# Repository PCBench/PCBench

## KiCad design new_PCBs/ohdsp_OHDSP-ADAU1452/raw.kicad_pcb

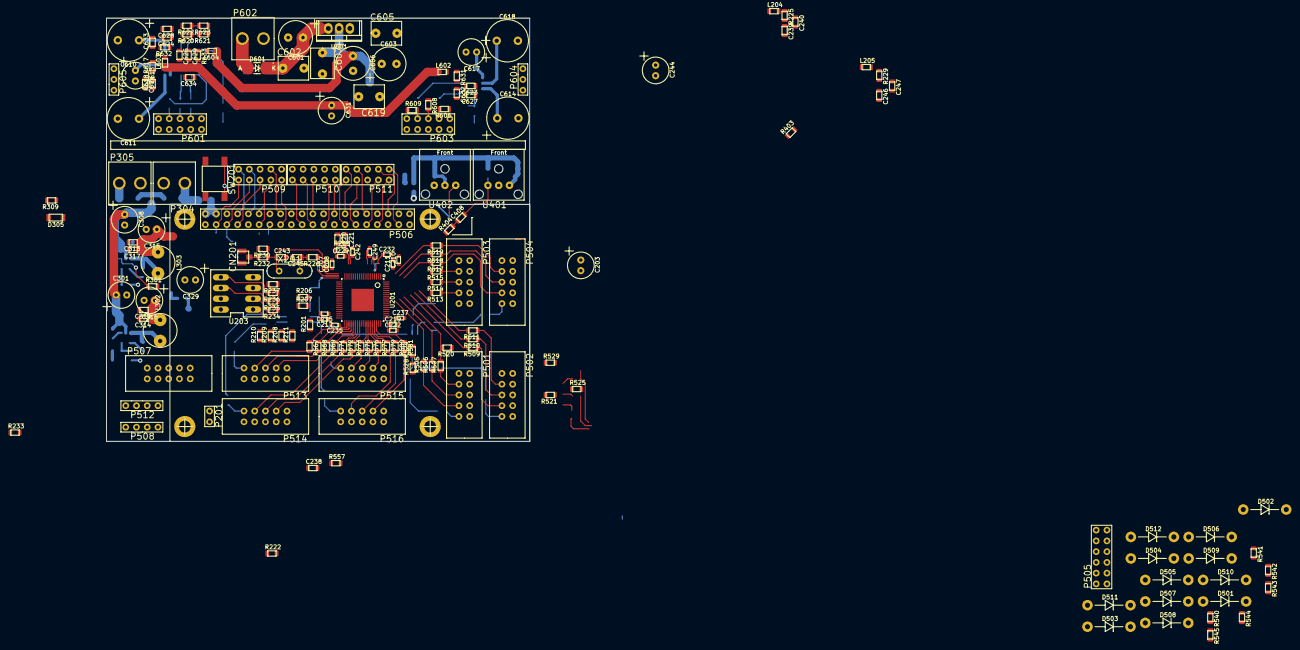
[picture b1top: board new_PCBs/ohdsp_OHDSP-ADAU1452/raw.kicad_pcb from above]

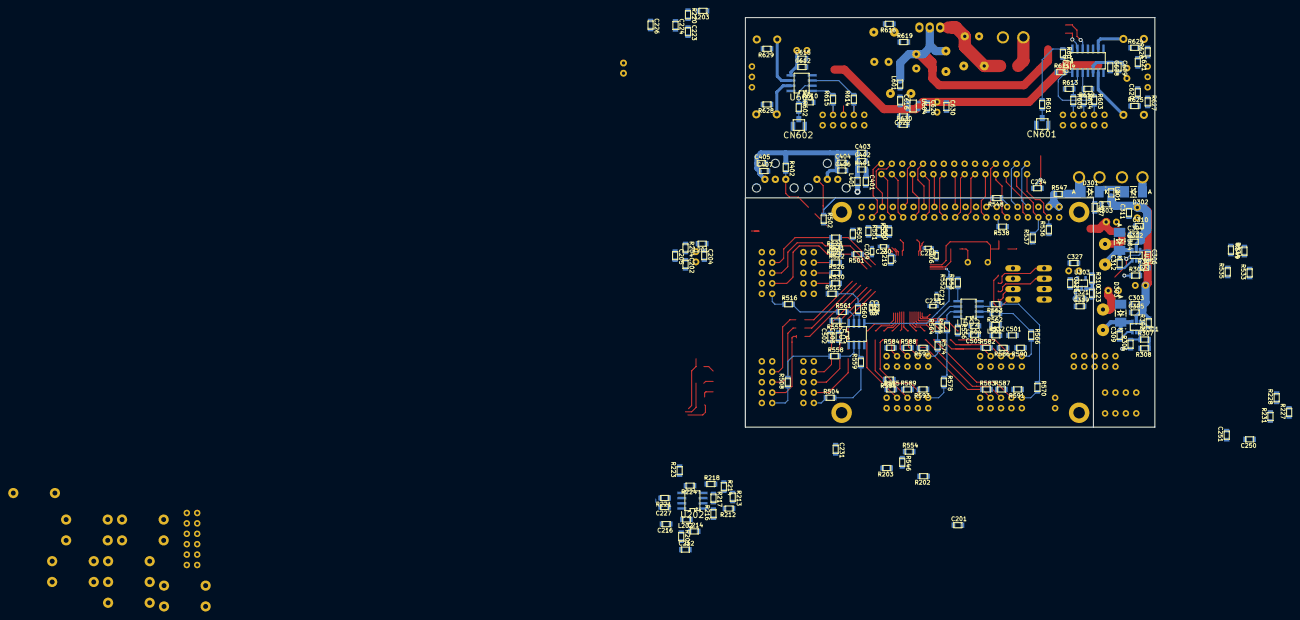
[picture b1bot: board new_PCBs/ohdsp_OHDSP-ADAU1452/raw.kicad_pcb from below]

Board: 4 copper layers, 100.0 x 100.0 mm, 376 parts (188 on the bottom side), 240 nets.

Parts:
C201, C205, C216, C226, C227, C231, C234, C238, C250, C304, C305, C311, C317, C318, C321, C325, C403, C406, C407, C503, C505, C604, C608, C612, C623, C624, C625, C626: 100n; SMD-0805
C202, C212, C223, C239, C246, C307, C401, C501, C632, C633, C634: 100p; SMD-0805
C203, C244, C301, C308, C315, C316, C329: 220u; CAP-TH-D6.3mmP2.5mm
C204, C224, C240, C247, C302, C303, C310, C313, C314, C319, C327, C402, C404, C405, C502, C504, C609, C615, C616, C627, C628, C629, C630: 22u; SMD-0805
C206, C209, C213, C218, C228, C230, C233, C236: 1u; SMD-0603
C207, C210, C215, C219, C229, C232, C235, C237, C242, C249: 100n; SMD-0603
C208, C211, C217, C222: 10n; SMD-0603
C214, C251, C306, C323: 1u; SMD-0805
C220: 5n6; SMD-0805
C221: 150p; SMD-0805
C243, C245: 33p; SMD-0805
C309, C312, C408, C622: 10n; SMD-0805
C601, C603, C606: 220u; CAP-TH-D8mmP3.5mm
C602, C605, C607, C619: 10n; CAP_TH_5mm
C610, C611, C614, C618: 100u; CAP-TH-D10mmP5mm
C613, C617, C631: 100u; CAP-TH-D6.3mmP2.5mm
C620, C621: 1n; SMD-0805
CN201, CN601, CN602: COAX; CONN-RF-UFL
D301, D302, D303, D304, D601: SS24T3G; DIODE-SMB
D305: LED; SMD-1206
D501, D502, D503, D504, D505, D506, D507, D508, D509, D510, D511, D512: 1N5818; DIODE-DO-41
L201, L202, L203, L204, L205, L301, L401, L501, L601, L602, L603, L604: 600R@100MHz; SMD-0805
L302: 744772220; PASSIVE-TH-IND-WURTH-5mm
L303: 744772047; PASSIVE-TH-IND-WURTH-5mm
P201: CONN_2x1; CONN_SIL_2
P301, P302, P303, P306: PIN; MNT_HOLE_2.5mm
P304, P305, P602: CONN_2x1; CONN-SCREW-2WAY-5mm-5.08mm
P501, P502, P503, P504, P507, P513, P514, P515, P516: CONN_02X05; CONN_DIL_2X5_BOX
P505: CONN_6X2; CONN_DIL_2X6
P506: CONN_02X20; CONN_DIL_2X20
P508, P512: CONN_4x1; CONN_SIL_4
P509, P510, P511, P601, P603: CONN_02X05; CONN_DIL_2X5
P604, P605: CONN_3x1; CONN_SIL_3
R201, R221, R538, R555, R556: 1k; SMD-0805
R202, R203, R626, R627: 2k2; SMD-0805
R204, R205, R220, R225, R229, R303, R401, R532, R631, R632, R633: 47R; SMD-0805
R206, R207, R212, R219, R234, R235, R236, R237, R308, R403, R504, R505, R506, R507, R508, R509, R510, R511, R512, R513, R514, R515, R516, R517, R518, R519, R533, R534, R535, R536, R537, R539, R546, R547, R548, R549, R550, R551, R554, R557, R601, R602, R614, R615: 0R; SMD-0805
R208, R209, R216, R230, R232, R233, R501, R502, R503, R520, R521, R522, R523, R524, R525, R526, R527, R528, R529, R530, R531, R582, R583, R584, R585, R586, R587, R588, R589, R590, R591, R592, R593, R594, R606, R607, R609, R610, R611, R612, R613, R618, R621, R623: N/F; SMD-0805
R210, R211, R227, R228, R231, R307, R402, R608, R617, R620, R622, R624, R625, R628, R629, R630: 10k; SMD-0805
R213: 12k; SMD-0805
R214: 3k3; SMD-0805
R215: 4k3; SMD-0805
R217: 3k; SMD-0805
R218: 3k6; SMD-0805
R222, R223, R226: 100R; SMD-0805
R224, R301, R302, R310: 100k; SMD-0805
R304: 47k; SMD-0805
R305: 97k6; SMD-0805
R306: 39k; SMD-0805
R309: 470R; SMD-0805
R404: 22R; SMD-0805
R540, R541, R542, R543, R544, R545: 4k7; SMD-0805
R552, R553: 75R; SMD-0805
R558, R559, R560, R561, R562, R563, R564, R565, R566, R567, R568, R569, R570, R571, R572, R573, R574, R575, R576, R577, R578, R579, R580, R581, R603, R604, R605: 27R; SMD-0805
R616: 360R; SMD-0805
R619: 120R; SMD-0805
SW201: SWITCH; SW_TACT_SMD
U201: ADAU1452WBCPZ; IC-LFCSP72-HANDFIT
U202: ADM13307-5ARZ; IC_SOIC_8
U203: 25AA1024; IC_DIP_8
U301, U302: IC-REG-XRP7659ISTR-F; IC-SOT23-6
U303, U604: IC-REG-XC6210B332MR; IC-SOT25
U401: IC-SPDIF-RX-OPTO; IC_SPDIF_OPTO
U402: IC-SPDIF-TX-OPTO; IC_SPDIF_OPTO
U501, U502: NB3L553; IC_SOIC_8
U601: IC-REG-LM317-TO220; TO-220
U602: IC-DAC-WM8501; IC_SOIC_14
U603: IC-ADC-WM8783; IC_SOIC_8
X201: 24M576; XTAL_HC49_TH

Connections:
+5V: D301.1, P304.1, R547.2
/ADAU1452/ADAU_SPDIF_RX: R404.1, U201.4
/ADAU1452/ADAU_SPDIF_TX: R403.1, U201.5
/ADAU1452/ADCIN_BCLK0: R506.2, R524.2, U201.58
/ADAU1452/ADCIN_BCLK1: R510.2, R525.2, U201.61
/ADAU1452/ADCIN_BCLK2: R514.2, R526.2, U201.66
/ADAU1452/ADCIN_BCLK3: R502.2, R518.2, R527.2, U201.69
/ADAU1452/ADCIN_LRCLK0: R505.2, R528.2, U201.57
/ADAU1452/ADCIN_LRCLK1: R509.2, R529.2, U201.60
/ADAU1452/ADCIN_LRCLK2: R513.2, R530.2, U201.65
/ADAU1452/ADCIN_LRCLK3: R501.2, R517.2, R531.2, U201.68
/ADAU1452/ADCIN_SDATA0: R507.2, R520.2, U201.59
/ADAU1452/ADCIN_SDATA1: R511.2, R521.2, U201.62
/ADAU1452/ADCIN_SDATA2: R515.2, R522.2, U201.67
/ADAU1452/ADCIN_SDATA3: R503.2, R519.2, R523.2, U201.70
/ADAU1452/AVDD: C247.1, C249.1, L205.2, R229.1, U201.7
/ADAU1452/DACOUT_BCLK0: R568.1, U201.40
/ADAU1452/DACOUT_BCLK1: R572.1, U201.43
/ADAU1452/DACOUT_BCLK2: R576.1, U201.48
/ADAU1452/DACOUT_BCLK3: R580.1, U201.51
/ADAU1452/DACOUT_LRCLK0: R567.1, U201.39
/ADAU1452/DACOUT_LRCLK1: R571.1, U201.42
/ADAU1452/DACOUT_LRCLK2: R575.1, U201.47
/ADAU1452/DACOUT_LRCLK3: R579.1, U201.50
/ADAU1452/DACOUT_SDATA0: R569.1, U201.41
/ADAU1452/DACOUT_SDATA1: R573.1, U201.44
/ADAU1452/DACOUT_SDATA2: R577.1, U201.49
/ADAU1452/DACOUT_SDATA3: R581.1, U201.52
/ADAU1452/DSP_RESET: C238.1, R222.1, U201.24
/ADAU1452/DVDD: C203.1, C204.1, C205.1, C206.1, C207.1, C208.1, C209.1, C210.1, C211.1, C213.1, C215.1, C217.1, C218.1, C219.1, C222.1, L201.2, R204.1, U201.20, U201.35, U201.53, U201.71
/ADAU1452/GLB_RESET: R223.1, R546.1, R557.1
/ADAU1452/I2C_SCL: P507.1, P508.1, P512.1, R202.2, R207.1, R537.1
/ADAU1452/I2C_SDA: P507.3, P508.2, P512.2, R203.2, R206.1, R536.1
/ADAU1452/IOVDD: C224.1, C226.1, C228.1, C229.1, C230.1, C232.1, C233.1, C235.1, C236.1, C237.1, L203.2, R208.1, R209.1, R220.1, U201.2, U201.18, U201.38, U201.56
/ADAU1452/MAN_RST_IN: C234.1, R221.2, R538.1, R554.2, SW201.1
/ADAU1452/MCLK: R552.2, R553.2, U201.23
/ADAU1452/M_MISO: R233.2, R234.2, U203.2
/ADAU1452/M_MOSI: R236.2, U203.5
/ADAU1452/M_SCLK: R235.2, U203.6
/ADAU1452/M_SS: R227.2, R237.2, U203.1
/ADAU1452/PVDD: C220.1, C221.1, C240.1, C242.1, L204.2, R225.1, U201.15
/ADAU1452/SELFBOOT: P201.1, R201.2, U201.34
/ADAU1452/XTALIN: C243.1, R230.1, R232.1, U201.21, X201.1
/ADAU1452/XTALOUT: R226.1, U201.22
/Connectors/AUXADCIN_1: D501.1, D502.2, R540.2, U201.8
/Connectors/AUXADCIN_2: D503.1, D504.2, R541.2, U201.9
/Connectors/AUXADCIN_3: D505.1, D506.2, R542.2, U201.10
/Connectors/AUXADCIN_4: D507.1, D508.2, R543.2, U201.11
/Connectors/AUXADCIN_5: D509.1, D510.2, R544.2, U201.12
/Connectors/AUXADCIN_6: D511.1, D512.2, R545.2, U201.13
/Connectors/MCLKA1: R508.2, R558.1
/Connectors/MCLKA2: R504.2, R559.1
/Connectors/MCLKA3: R512.2, R560.1
/Connectors/MCLKA4: R516.2, R561.1
/Connectors/MCLKB1: R562.1, R566.1
/Connectors/MCLKB2: R563.1, R570.1
/Connectors/MCLKB3: R564.1, R574.1
/Connectors/MCLKB4: R565.1, R578.1
/Connectors/PI_GP4: P506.7, P509.5
/Connectors/PI_GP5: P506.29, P511.3
/Connectors/PI_GP6: P506.31, P511.7
/Connectors/PI_GP12: P506.32, P511.4
/Connectors/PI_GP13: P506.33, P511.9
/Connectors/PI_GP14: P506.8, P509.2
/Connectors/PI_GP15: P506.10, P509.4
/Connectors/PI_GP16: P506.36, P511.8
/Connectors/PI_GP17: P506.11, P509.7
/Connectors/PI_GP22: P506.15, P509.9
/Connectors/PI_GP23: P506.16, P509.8
/Connectors/PI_GP24: P506.18, P509.10
/Connectors/PI_GP25: P506.22, P510.5
/Connectors/PI_GP26: P506.37, P511.10
/Connectors/PI_IDSC: P506.28, P511.2
/Connectors/PI_IDSD: P506.27, P511.1
/Connectors/PI_MISO: P506.21, P510.3, R534.2
/Connectors/PI_MOSI: P506.19, P510.1, R533.2
/Connectors/PI_SCL: P506.5, P509.3, R537.2
/Connectors/PI_SCLK: P506.23, P510.7, R535.2
/Connectors/PI_SDA: P506.3, P509.1, R536.2
/Connectors/RPI_BCLK: R502.1, R548.2
/Connectors/RPI_CS2: P506.26, P510.9
/Connectors/RPI_LRCLK: R501.1, R539.1
/Connectors/RPI_SDATA_IN: R550.2, R594.2
/Connectors/RPI_SDATA_OUT: R503.1, R551.2
/SimpleADCDAC/ADC_AVDD: C623.1, C627.1, L602.2, R631.1, U603.8
/SimpleADCDAC/DAC5v: C606.1, C607.1, L601.2, L604.1, R619.2, U601.2
/SimpleADCDAC/DAC_AVDD: C625.1, C629.1, L604.2, R633.1, U602.8
/SimpleADCDAC/DAC_DVDD: C624.1, C628.1, L603.2, R617.2, R620.2, R622.2, R632.1, U602.11
/SimpleADCDAC/DEMP: R622.1, R623.2, U602.12
/SimpleADCDAC/EN: C604.1, R617.1, R618.2, U602.4
/SimpleADCDAC/FMT: R620.1, R621.2, U602.13
GNDA: C601.2, C602.2, C603.2, C604.2, C605.2, C606.2, C607.2, C608.2, C609.2, C612.2, C613.2, C615.2, C616.2, C617.2, C619.2, C620.2, C621.2, C622.2, C623.2, C624.2, C625.2, C626.2, C627.2, C628.2, C629.2, C630.2, C631.2, C632.2, C633.2, C634.2, CN601.2, CN602.2, P601.1, P601.2, P601.3, P601.5, P601.7, P601.9, P601.10, P602.2, P603.1, P603.2, P603.3, P603.5, P603.7, P603.9, P603.10, P604.2, P605.2, R606.1, R607.2, R608.1, R609.1, R610.2, R611.1, R612.1, R613.1, R616.2, R618.1, R621.1, R623.1, R624.1, R625.1, R628.1, R629.1, U602.7, U602.10, U603.4, U604.2
GNDD: C201.2, C202.2, C203.2, C204.2, C205.2, C206.2, C207.2, C208.2, C209.2, C210.2, C211.2, C212.2, C213.2, C214.2, C215.2, C216.2, C217.2, C218.2, C219.2, C222.2, C223.2, C224.2, C226.2, C227.2, C228.2, C229.2, C230.2, C231.2, C232.2, C233.2, C234.2, C235.2, C236.2, C237.2, C238.2, C239.2, C240.2, C242.2, C243.2, C244.2, C245.2, C246.2, C247.2, C249.2, C250.2, C251.2, C301.2, C302.1, C303.1, C304.1, C305.1, C306.2, C307.2, C308.2, C310.1, C311.1, C313.2, C314.2, C315.2, C316.2, C317.2, C318.2, C319.2, C321.2, C323.2, C325.2, C327.2, C329.2, C401.2, C402.2, C403.2, C404.2, C405.2, C406.2, C407.2, C501.2, C502.2, C503.2, C504.2, C505.2, CN201.2, D303.1, D304.1, D305.2, D502.1, D504.1, D506.1, D508.1, D510.1, D512.1, P201.2, P301.1, P302.1, P303.1, P304.2, P305.2, P306.1, P501.1, P501.3, P501.5, P501.7, P501.9, P501.10, P502.1, P502.3, P502.5, P502.7, P502.9, P502.10, P503.1, P503.3, P503.5, P503.7, P503.9, P503.10, P504.1, P504.3, P504.5, P504.7, P504.9, P504.10, P505.1, P505.3, P505.5, P505.7, P505.9, P505.11, P506.6, P506.9, P506.14, P506.20, P506.25, P506.30, P506.34, P506.39, P508.3, P509.6, P510.2, P510.4, P510.6, P510.8, P510.10, P511.5, P511.6, P512.3, P513.1, P513.3, P513.5, P513.7, P513.9, P513.10, P514.1, P514.3, P514.5, P514.7, P514.9, P514.10, P515.1, P515.3, P515.5, P515.7, P515.9, P515.10, P516.1, P516.3, P516.5, P516.7, P516.9, P516.10, R210.1, R211.1, R216.1, R217.1, R218.1, R219.1, R224.1, R230.2, R305.2, R308.2, R520.1, R521.1, R522.1, R523.1, R524.1, R525.1, R526.1, R527.1, R528.1, R529.1, R530.1, R531.1, R582.1, R583.1, R584.1, R585.1, R586.1, R587.1, R588.1, R589.1, R590.1, R591.1, R592.1, R593.1, SW201.2, U201.1, U201.6, U201.14, U201.17, U201.19, U201.25, U201.36, U201.37, U201.54, U201.55, U201.72, U201.EP1, U202.4, U203.4, U301.2, U302.2, U303.2, U401.2, U402.3, U501.4, U502.4
unnamed: C202.1, R204.2
unnamed: C212.1, R205.2
unnamed: C214.1, C216.1, L202.2, R205.1, U202.8
unnamed: C220.2, R215.1
unnamed: C221.2, R215.2, U201.16
unnamed: C223.1, R220.2
unnamed: C227.1, R221.1, U202.7
unnamed: C231.1, R222.2, R223.2, R224.2, U202.6
unnamed: C239.1, R225.2
unnamed: C245.1, R226.2, X201.2
unnamed: C246.1, R229.2
unnamed: C306.1, R301.1, U302.4
unnamed: C307.1, R303.2
unnamed: C309.1, U301.1
unnamed: C309.2, D303.2, L302.1, U301.6
unnamed: C312.1, U302.1
unnamed: C312.2, D304.2, L303.1, U302.6
unnamed: C323.1, R310.2, U303.3
unnamed: C401.1, R401.2
unnamed: C402.1, C403.1, C404.1, C405.1, C406.1, C407.1, L401.2, R401.1, R402.1, U401.1, U402.2
unnamed: C408.1, R404.2
unnamed: C408.2, R402.2, U401.3
unnamed: C501.1, R532.2
unnamed: C502.1, C503.1, C504.1, C505.1, L501.2, R532.1, R555.2, R556.2, U501.1, U502.1
unnamed: C601.1, C602.1, D601.2, U601.3
unnamed: C603.1, C605.1, R616.1, R619.1, U601.1
unnamed: C608.1, C609.1, C613.1, U602.5
unnamed: C610.1, U602.9
unnamed: C610.2, R624.2, R626.2
unnamed: C611.1, U602.6
unnamed: C611.2, R625.2, R627.2
unnamed: C612.1, C615.1, C617.1, U603.5
unnamed: C614.1, U603.7
unnamed: C614.2, P604.1, R628.2
unnamed: C616.1, C619.1, L601.1, R630.1, U604.1
unnamed: C618.1, U603.6
unnamed: C618.2, P604.3, R629.2
unnamed: C620.1, P605.3, R627.1
unnamed: C621.1, P605.1, R626.1
unnamed: C622.1, R630.2, U604.3
unnamed: C626.1, C630.1, C631.1, L602.1, L603.1, U604.5
unnamed: C632.1, R631.2
unnamed: C633.1, R632.2
unnamed: C634.1, R633.2
unnamed: CN201.1, R232.2
unnamed: CN601.1, R601.2
unnamed: CN602.1, R602.2
unnamed: D301.2, D302.2, L301.1
unnamed: D302.1, P305.1
unnamed: D305.1, R309.2
unnamed: D601.1, P602.1
unnamed: P501.2, R504.1
unnamed: P501.4, R505.1
unnamed: P501.6, R506.1
unnamed: P501.8, R507.1
unnamed: P502.2, R508.1
unnamed: P502.4, R509.1
unnamed: P502.6, R510.1
unnamed: P502.8, R511.1
unnamed: P503.2, R512.1
unnamed: P503.4, R513.1
unnamed: P503.6, R514.1
unnamed: P503.8, R515.1
unnamed: P504.2, R516.1
unnamed: P504.4, R517.1
unnamed: P504.6, R518.1
unnamed: P504.8, R519.1
unnamed: P505.2, R540.1
unnamed: P505.4, R541.1
unnamed: P505.6, R542.1
unnamed: P505.8, R543.1
unnamed: P505.10, R544.1
unnamed: P505.12, R545.1
unnamed: P506.2, P506.4, R547.1
unnamed: P506.12, R548.1
unnamed: P506.13, R538.2
unnamed: P506.24, R549.1
unnamed: P506.35, R539.2
unnamed: P506.38, R550.1
unnamed: P506.40, R551.1
unnamed: P507.6, R554.1
unnamed: P508.4, R546.2
unnamed: P512.4, R557.2
unnamed: P513.2, R566.2
unnamed: P513.4, R567.2, R590.2
unnamed: P513.6, R568.2, R586.2
unnamed: P513.8, R569.2, R582.2
unnamed: P514.2, R570.2
unnamed: P514.4, R571.2, R591.2
unnamed: P514.6, R572.2, R587.2
unnamed: P514.8, R573.2, R583.2
unnamed: P515.2, R574.2
unnamed: P515.4, R575.2, R592.2
unnamed: P515.6, R576.2, R588.2
unnamed: P515.8, R577.2, R584.2
unnamed: P516.2, R578.2
unnamed: P516.4, R579.2, R593.2
unnamed: P516.6, R580.2, R589.2
unnamed: P516.8, R581.2, R585.2, R594.1
unnamed: P601.4, R603.2
unnamed: P601.6, R604.2
unnamed: P601.8, R605.2
unnamed: P603.4, R609.2, R614.1
unnamed: P603.6, R608.2
unnamed: P603.8, R606.2, R615.1
unnamed: R206.2, U201.30
unnamed: R207.2, U201.31
unnamed: R208.2, R211.2, U201.33
unnamed: R209.2, R210.2, U201.32
unnamed: R212.2, R216.2, U202.1
unnamed: R213.2, R217.2, U202.2
unnamed: R214.2, R218.2, U202.3
unnamed: R219.2, U201.3
unnamed: R228.2, U203.3
unnamed: R231.2, U203.7
unnamed: R234.1, U201.29
unnamed: R235.1, U201.28
unnamed: R236.1, U201.27
unnamed: R237.1, U201.26
unnamed: R302.1, U301.4
unnamed: R304.2, R305.1, U302.3
unnamed: R306.2, R307.1, U301.3
unnamed: R307.2, R308.1
unnamed: R403.2, U402.1
unnamed: R552.1, U501.5
unnamed: R553.1, U502.5
unnamed: R555.1, U501.8
unnamed: R556.1, U502.8
unnamed: R558.2, U501.2
unnamed: R559.2, U501.3
unnamed: R560.2, U501.6
unnamed: R561.2, U501.7
unnamed: R562.2, U502.2
unnamed: R563.2, U502.3
unnamed: R564.2, U502.6
unnamed: R565.2, U502.7
unnamed: R601.1, R607.1, U602.14
unnamed: R602.1, R610.1, U603.2
unnamed: R603.1, R611.2, U602.1
unnamed: R604.1, R612.2, U602.3
unnamed: R605.1, R613.2, U602.2
unnamed: R614.2, U603.3
unnamed: R615.2, U603.1
VAA: C201.1, C244.1, C250.1, C251.1, C325.1, C327.1, C329.1, D501.2, D503.2, D505.2, D507.2, D509.2, D511.2, L202.1, L203.1, L204.1, L205.1, L401.1, L501.1, R201.1, R202.1, R203.1, R212.1, R213.1, R227.1, R228.1, R231.1, R233.1, R301.2, R309.1, U203.8, U303.5
VCC: C301.1, C302.2, C303.2, C304.2, C305.2, C308.1, C310.2, C311.2, L301.2, R302.2, R303.1, U301.5, U302.5
VCOM: C314.1, C316.1, C318.1, C319.1, C321.1, L302.2, R306.1, R310.1, U303.1
VDD: C313.1, C315.1, C317.1, L201.1, L303.2, R214.1, R304.1

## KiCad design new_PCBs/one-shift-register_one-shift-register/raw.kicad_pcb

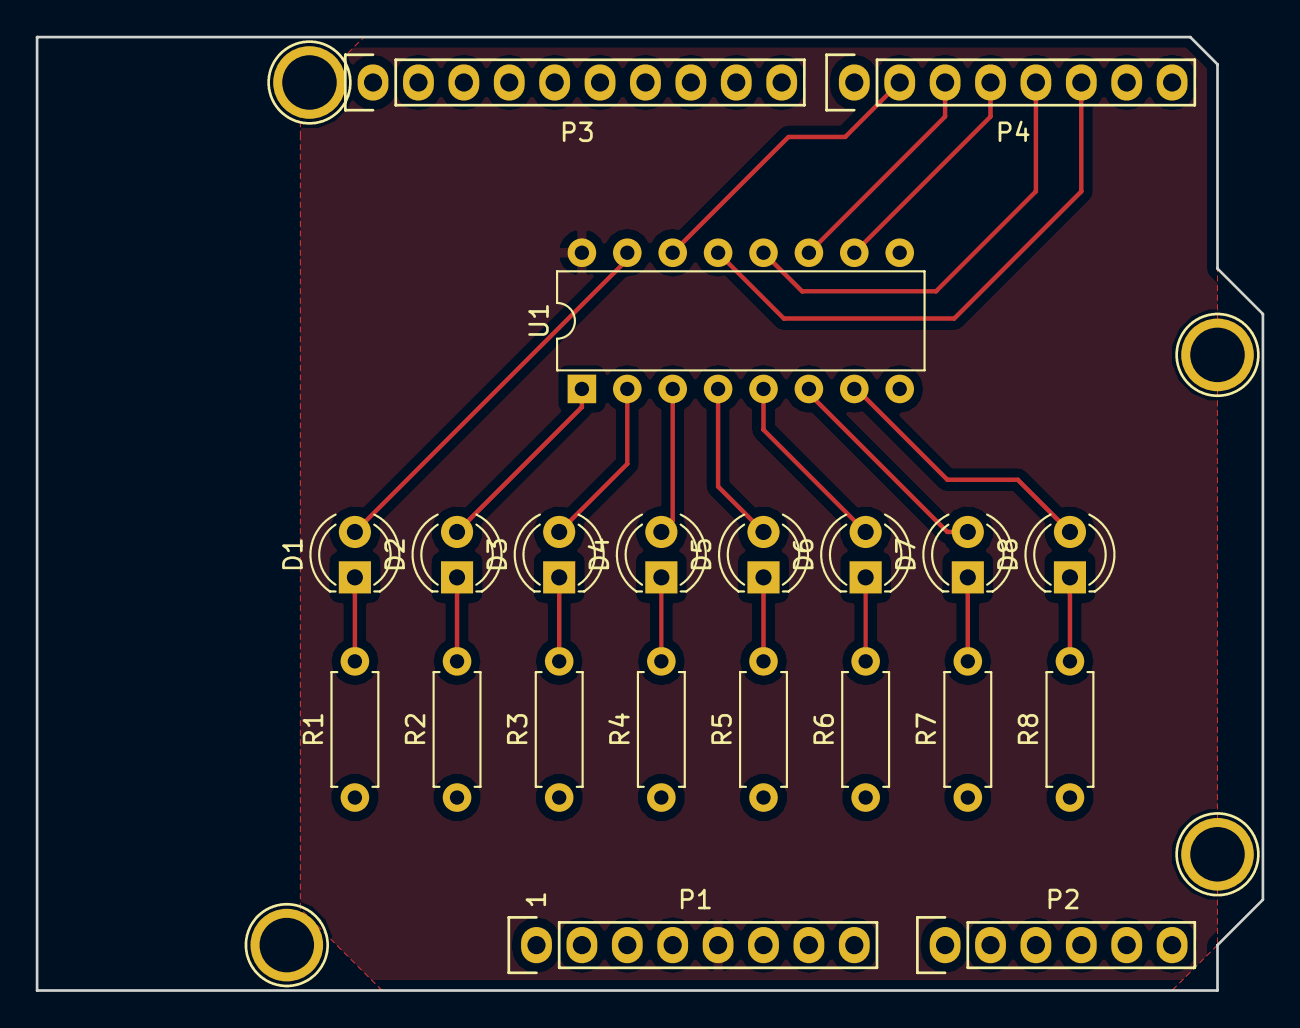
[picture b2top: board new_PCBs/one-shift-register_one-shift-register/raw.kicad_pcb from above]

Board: 2 copper layers, 68.6 x 53.3 mm, 25 parts (0 on the bottom side), 23 nets.

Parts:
D1, D2, D3, D4, D5, D6, D7, D8: LED; LED_D4.0mm
P1: Power; Socket_Strip_Arduino_1x08
P2: Analog; Socket_Strip_Arduino_1x06
P3: Digital; Socket_Strip_Arduino_1x10
P4: Digital; Socket_Strip_Arduino_1x08
P5, P6, P7, P8: CONN_1; Arduino_1pin
R1, R2, R3, R4, R5, R6, R7, R8: 220; R_Axial_DIN0207_L6.3mm_D2.5mm_P7.62mm_Horizontal
U1: 74HC595; DIP-16_W7.62mm

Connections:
+5V: P1.5, U1.16
/2: P4.6, U1.13
/3(**): P4.5, U1.12
/4: P4.4, U1.10
/5(**): P4.3, U1.11
/6(**): P4.2, U1.14
GND: P1.6, P1.7, P3.4, R1.1, R2.1, R3.1, R4.1, R5.1, R6.1, R7.1, R8.1, U1.8
unnamed: D1.1, R1.2
unnamed: D1.2, U1.15
unnamed: D2.1, R2.2
unnamed: D2.2, U1.1
unnamed: D3.1, R3.2
unnamed: D3.2, U1.2
unnamed: D4.1, R4.2
unnamed: D4.2, U1.3
unnamed: D5.1, R5.2
unnamed: D5.2, U1.4
unnamed: D6.1, R6.2
unnamed: D6.2, U1.5
unnamed: D7.1, R7.2
unnamed: D7.2, U1.6
unnamed: D8.1, R8.2
unnamed: D8.2, U1.7

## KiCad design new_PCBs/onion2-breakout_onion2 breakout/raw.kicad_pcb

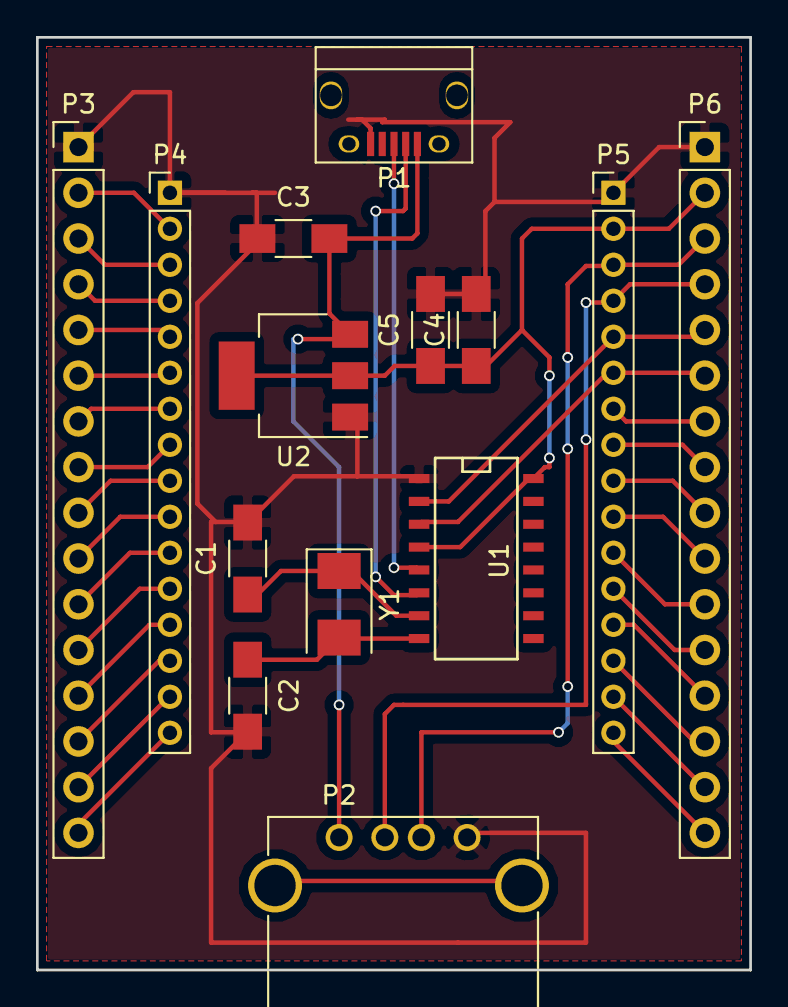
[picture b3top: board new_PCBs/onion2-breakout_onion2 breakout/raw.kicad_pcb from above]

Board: 2 copper layers, 39.6 x 51.8 mm, 14 parts (0 on the bottom side), 36 nets.

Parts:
C1, C2: 22pF; C_1206_HandSoldering
C3: 100uF; C_1206_HandSoldering
C4: 10uF; C_1206_HandSoldering
C5: 0.1uF; C_1206_HandSoldering
P1: USB_B; USB_Micro-B
P2: USB_B; USB_A
P3, P6: CONN_01X16; Pin_Header_Straight_1x16_Pitch2.54mm
P4, P5: CONN_01X16; Pin_Header_Straight_1x16_Pitch2.00mm
U1: CH340G; SO-16-N
U2: AP1117; SOT-223
Y1: 12MHz; Crystal_SMD_5032-2pin_5.0x3.2mm

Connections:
+3V3: C4.1, C5.1, P5.2, P6.2, U1.4, U1.16, U2.2, U2.4
+5V: C3.2, P1.1, P2.1, U2.3
D2+: P2.3, P5.3, P6.3
D2-: P2.2, P5.4, P6.4
D+: P1.3, U1.5
D-: P1.2, U1.6
GND: C1.2, C2.2, C3.1, C4.2, C5.2, P1.5, P2.4, P3.1, P4.1, P5.1, P6.1, U1.1, U2.1
unnamed: C1.1, U1.7, Y1.1
unnamed: C2.1, U1.8, Y1.2
unnamed: P3.2, P4.2
unnamed: P3.3, P4.3
unnamed: P3.4, P4.4
unnamed: P3.5, P4.5
unnamed: P3.6, P4.6
unnamed: P3.7, P4.7
unnamed: P3.8, P4.8
unnamed: P3.9, P4.9
unnamed: P3.10, P4.10
unnamed: P3.11, P4.11
unnamed: P3.12, P4.12
unnamed: P3.13, P4.13
unnamed: P3.14, P4.14
unnamed: P3.15, P4.15
unnamed: P3.16, P4.16
unnamed: P5.7, P6.7
unnamed: P5.8, P6.8
unnamed: P5.9, P6.9
unnamed: P5.10, P6.10
unnamed: P5.11, P6.11
unnamed: P5.12, P6.12
unnamed: P5.13, P6.13
unnamed: P5.14, P6.14
unnamed: P5.15, P6.15
unnamed: P5.16, P6.16
RxD: P5.5, P6.5, U1.2
TxD: P5.6, P6.6, U1.3

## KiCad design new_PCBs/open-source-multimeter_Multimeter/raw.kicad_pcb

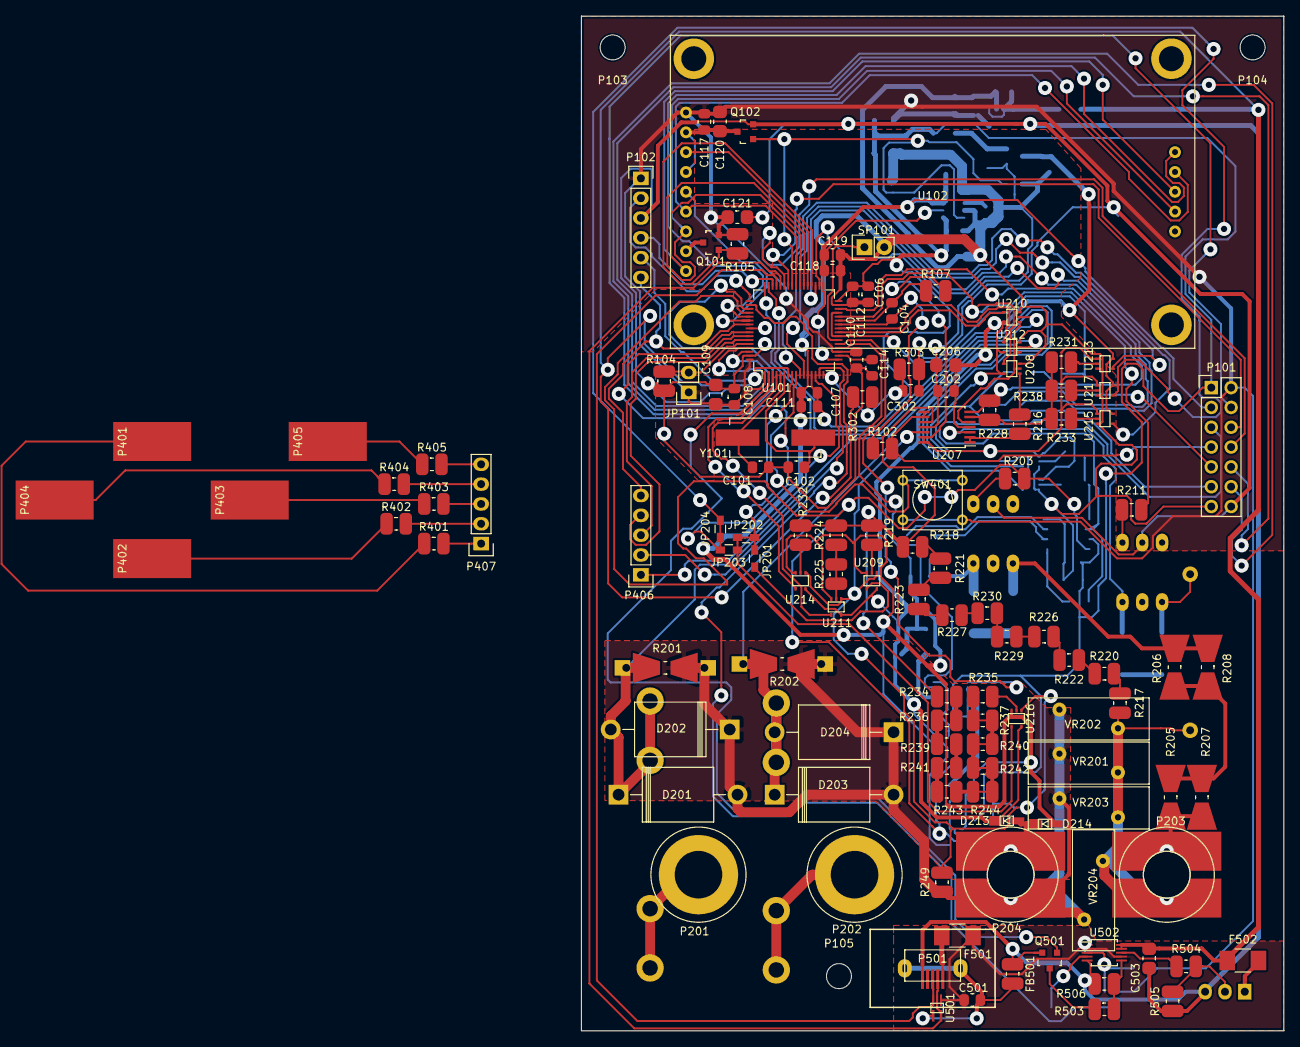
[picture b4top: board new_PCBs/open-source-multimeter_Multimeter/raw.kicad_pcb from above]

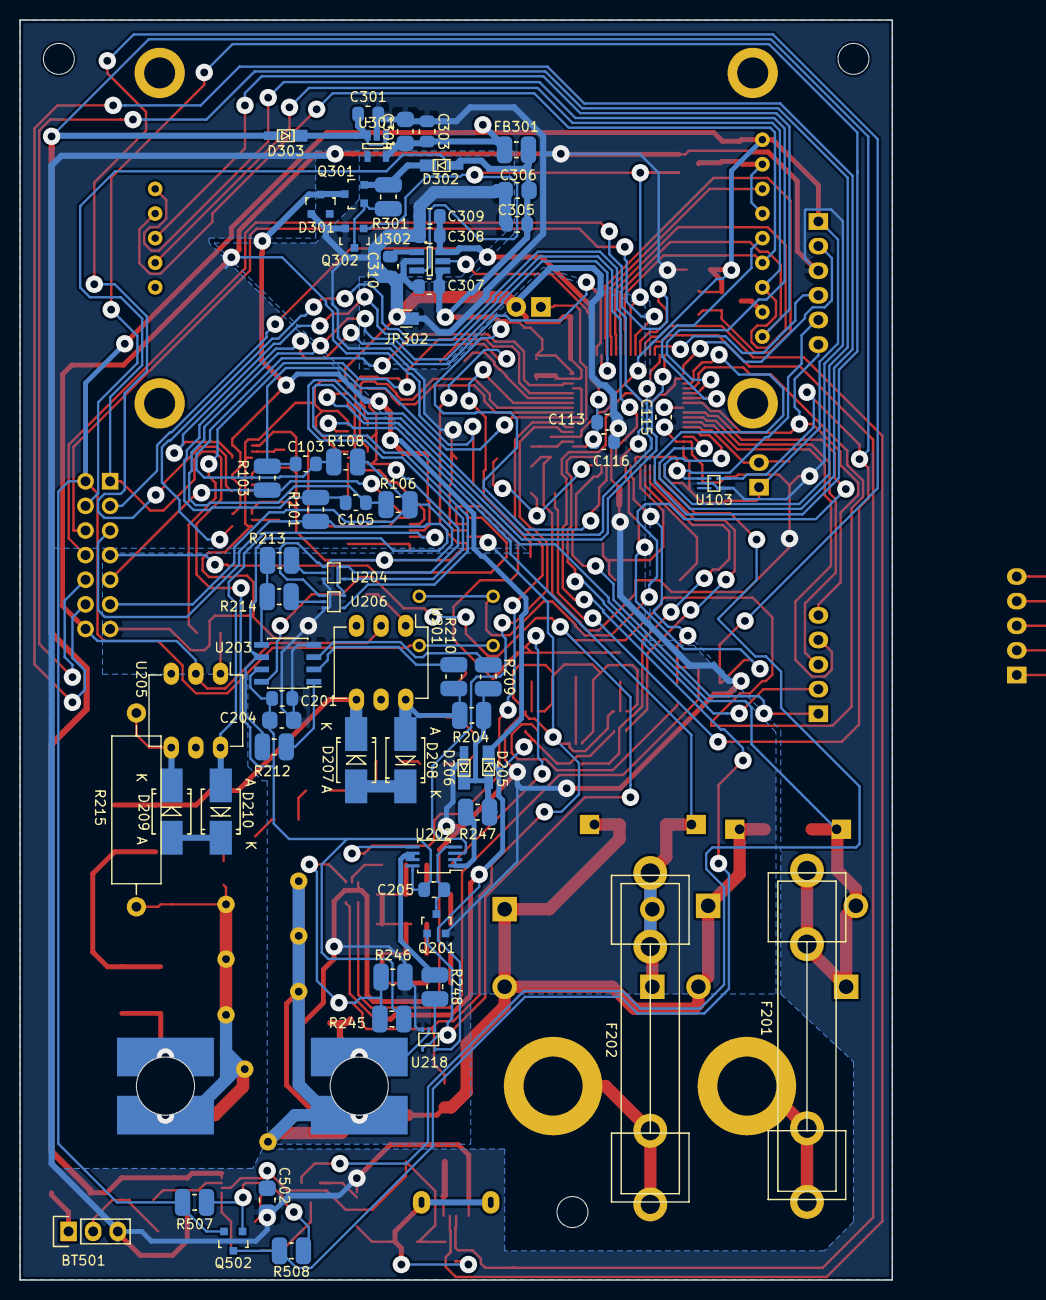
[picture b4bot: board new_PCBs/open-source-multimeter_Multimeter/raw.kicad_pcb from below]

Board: 2 copper layers, 90.0 x 130.0 mm, 194 parts (64 on the bottom side), 146 nets.

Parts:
BT501: Li-Ion_Cell; Pin_Header_Straight_1x03
C101, C102: 18p; SMDuniversal_0603to0805_HandSoldering
C103, C104, C105: 3.9n; SMDuniversal_0603to0805_HandSoldering
C106, C107, C116, C119, C301, C302, C309: 1u; SMDuniversal_0603to0805_HandSoldering
C108, C110, C117, C201, C202, C205, C303, C305, C307, C310, C501: 0.1u; SMDuniversal_0603to0805_HandSoldering
C109, C120, C121, C204, C206, C304, C306, C502, C503: 10u; SMDuniversal_0603to1206_HandSoldering
C111, C112, C113, C118, C308: 0.01u; SMDuniversal_0603to0805_HandSoldering
C114, C115: 10n; SMDuniversal_0603to0805_HandSoldering
D201, D202, D203, D204: D; Diode_R-6_Horizontal_RM15
D205, D206, D213, D214, D302, D303: D_Schottky; SC-90A
D207, D208, D209, D210: TVS; SMB_Handsoldering
D301: 3.6V; SOT-23
F201, F202: FUSE; Fuseholder6x32_horiz_open_inline_Type-I
F501, F502: 500mA; R_1210_HandSoldering
FB301, FB501: FILTER; SMDuniversal_0603to1210_HandSoldering
JP101: BOOT0; Pin_Header_Straight_1x02
JP201, JP203: Jumper_NO_Small; R_0603_HandSoldering
JP202, JP204: Jumper_NC_Small; R_0603_HandSoldering
JP302: Net_Tie
P101: Expansion header; Pin_Header_Straight_2x07
P102: Programming header; Pin_Header_Straight_1x06
P103, P104, P105: Mounting hole; MountingHole_3.2mm_M3
P201: 10 A; Banana_Jack_1Pin
P202: mA; Banana_Jack_1Pin
P203: V R; Banana_Jack_1Pin_2Contact_SM_Top
P204: COMMON; Banana_Jack_1Pin_2Contact_SM_Top
P401, P402, P403, P404, P405: CONN_01X01; SolderWirePad_single_SMD_5x10mm
P406, P407: CONN_01X05; Pin_Header_Straight_1x05
P501: USB_OTG; MicroUSB_B_Vertical
Q101, Q301, Q502: Q_PMOS_GSD; SOT-23
Q102, Q201, Q302, Q501: Q_NMOS_GSD; SOT-23
R101, R102, R103, R106, R107, R108: 500R; SMDuniversal_0603to1210_HandSoldering
R104, R105, R212, R228, R301, R507: 100k; SMDuniversal_0603to1210_HandSoldering
R201: 10m; Resistor_SMD+THTuniversal_0805to2512_RM10_HandSoldering
R202: 100m; Resistor_SMD+THTuniversal_0805to2512_RM10_HandSoldering
R203, R211, R401, R402, R403, R404, R405, R508: 1k; SMDuniversal_0603to1210_HandSoldering
R204: 100R; SMDuniversal_0603to1210_HandSoldering
R205, R206, R207, R208: 1.8k; Resistor_SMDuniversal_0805to2512_HandSoldering
R209, R210, R216, R506: 10k; SMDuniversal_0603to1210_HandSoldering
R213, R214, R219, R224, R225, R231, R232, R233, R235, R237, R238, R504, R505: R; SMDuniversal_0603to1210_HandSoldering
R215: 100k; Resistor_Horizontal_RM20mm
R217, R218, R220, R221, R222, R223, R226, R227, R229, R230, R234, R236, R239, R240, R241, R242, R243, R244, R245, R246, R302, R303: 1M; SMDuniversal_0603to1210_HandSoldering
R247, R248, R249: 68R; SMDuniversal_0603to1210_HandSoldering
R503: 2.5k; SMDuniversal_0603to1210_HandSoldering
SP101: SPEAKER; Pin_Header_Straight_1x02
SW401: SW_PUSH; SW_PUSH_SMALL
U101: STM32F373R8Tx; LQFP-64_10x10mm_Pitch0.5mm
U102: ILI9341_LCD_Breakout
U103: BD4835; VSOF5_HandSoldering
U201, U205: CT138; DIP-6_W7.62mm_LongPads
U202: MCP6002; MSOP-8_3x3mm_Pitch0.65mm
U203: MCP6N11; SOIC-8_3.9x4.9mm_Pitch1.27mm
U204, U206, U208, U209, U210, U211, U212, U213, U214, U215, U216, U217, U218: 74LVC1G66 GNDA; SOT-353
U207: TSV634; TSSOP-14_4.4x5mm_Pitch0.65mm
U301: NCV551SN33T1G; SOT-23-5
U302: MAX6070; SOT-23-6_Handsoldering
U501: TPD2E001; VSOF5_HandSoldering
U502: MCP73834; MSOP-10_3x3mm_Pitch0.5mm
VR201, VR202, VR203, VR204: VR; RV_Disc_D15.5_W5.4_P7.5
Y101: 8 MHz; Crystal_HC49-SD_SMD

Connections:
+3.3VA: C106.2, C107.2, C111.2, C112.2, C201.1, C204.1, C205.1, C305.1, C306.1, C307.1, D302.2, FB301.2, P101.1, R245.1, U101.13, U101.32, U202.8, U203.7, U302.4
+3V3: C108.1, C109.2, C110.1, C117.1, C120.2, C121.1, C303.1, C304.1, FB301.1, JP101.1, P101.2, P102.1, Q101.2, Q502.2, R105.2, R507.2, SW401.2, U101.1, U101.19, U101.64, U102.1, U301.5
+5V: C501.2, C502.1, F501.1, U501.1, U502.1, U502.2, U502.7
+BATT: C503.1, D303.2, F502.1, R302.1, U103.5, U502.9, U502.10
+V_int: C202.1, C206.2, D205.1, D213.1, D301.3, Q301.3, U204.5, U206.5, U207.4, U208.5, U209.5, U210.5, U211.5, U212.5, U213.5, U214.5, U215.5, U216.5, U217.5, U218.5
+Vref: C113.1, C116.1, C118.2, C119.2, C308.1, C309.1, P101.3, U101.17, U101.33, U302.5, U302.6
/0.2V_R: U101.10, U215.4
/0.02V_R: U101.11, U213.4
/2.5A_EN: U101.25, U212.4
/2V_R: JP203.2, JP204.1, JP204.2, U101.9, U217.4
/15A_EN: U101.24, U210.4
/20V_R: JP201.2, JP202.1, JP202.2, JP203.1, U101.8, U216.4
/200V_R: U101.4, U211.4
/300V_R: U101.3, U214.4
/500mA_CHARGE: Q501.1, U101.2
/+Vout: U101.20, U202.3
/-Vout: U101.21, U202.5
/BOOT0: JP101.2, R104.1, U101.60
/COMMON_Io: C105.2, R106.1, U101.35
/COMMON_LV: C103.2, R108.1, U101.30
/COMMON_V: C104.2, R107.1, U101.27
/Controls/MenuD: P406.2, U101.15
/Controls/MenuL: P406.3, U101.58
/Controls/MenuOK: SW401.1, U101.57
/Controls/MenuR: P406.4, U101.59
/Controls/MenuU: P406.1, U101.14
/GPIO1: P101.4, U101.51
/GPIO2: P101.6, U101.42
/GPIO3: P101.8, U101.43
/GPIO4: P101.10, U101.61
/GPIO5: P101.12, U101.62
/Iout: C105.1, R101.1, U101.34
/LV_EN: R211.1, U101.28, U208.4
/LVin: C103.1, R103.1, U101.23, U101.29
/Main Input / Output/2.5A_Sense: D203.1, D204.2, F202.2, R202.2, U212.2
/Main Input / Output/15A_Sense: D201.1, D202.2, F201.2, R201.2, U210.2
/Main Input / Output/COM: R245.2, R246.1, R249.2, U207.12, U209.1, U211.1, U214.1, U216.1
/Main Input / Output/COMMON: P101.11, R106.2, R107.2, R108.2, U204.1, U206.1, U207.13, U207.14, U213.1, U215.1, U217.1
/Main Input / Output/COM_D: D201.2, D202.1, D203.2, D204.1, P204.1, R201.1, R202.1, R249.1, VR201.2, VR202.2, VR203.2, VR204.2
/Main Input / Output/Iout: P101.5, R101.2, R212.1, U203.6
/Main Input / Output/LVin: P101.9, R103.2, R228.1, U207.7
/Main Input / Output/Vin: P101.7, R102.2, U207.8, U207.9
/NRST: P102.5, U101.7, U103.1
/OSC_IN: C101.1, U101.5, Y101.1
/OSC_OUT: C102.1, U101.6, Y101.2
/PS_EN: Q102.1, Q302.1, U101.41, U302.3
/Power Supply/+BTsense: C302.1, R302.2, R303.1, U101.16
/R_lg: U101.47, U204.4
/R_sm: U101.48, U206.4
/SWCLK: P102.2, U101.49
/SWDIO: P102.4, U101.46
/SWO/HOLD: P102.6, P406.5, U101.55
/USB/CHARGE_STAT: Q502.3, R508.2, U101.50
/USB/USB_D+: P501.3, U101.45, U501.3
/USB/USB_D-: P501.2, U101.44, U501.2, U501.5
/Vin: C104.1, R102.1, U101.26
/Vout_EN: Q201.1, R203.1, U101.52, U203.8, U218.4
GNDA: C106.1, C107.1, C111.1, C112.1, C113.2, C116.2, C118.1, C119.1, C201.2, C202.2, C204.2, C206.1, C305.2, C306.2, C307.2, C308.2, C309.2, C310.2, D206.2, D214.2, D301.1, JP302.2, P101.13, Q201.2, Q302.2, R246.2, SP101.2, U101.12, U101.31, U203.4, U204.3, U206.3, U207.11, U208.3, U209.3, U210.3, U211.3, U212.3, U213.3, U214.3, U215.3, U216.3, U217.3, U218.3, U302.2
GNDD: BT501.3, C101.2, C102.2, C108.2, C109.1, C110.2, C114.1, C115.1, C121.2, C301.2, C302.2, C303.2, C304.2, C502.2, C503.2, FB501.1, JP302.1, P101.14, P102.3, P501.5, Q102.2, Q501.2, R104.2, R303.2, R505.2, R506.1, U101.63, U103.2, U103.4, U201.2, U205.2, U301.2, U502.5
unnamed: BT501.1, F502.2
unnamed: BT501.2, R504.1, R505.1
unnamed: C114.2, U101.18
unnamed: C115.2, U101.56
unnamed: C117.2, C120.1, Q102.3, U102.2, U102.4
unnamed: C205.2, Q201.3, U202.4
unnamed: C301.1, D303.1, U301.1, U301.3
unnamed: C310.1, U302.1
unnamed: C501.1, FB501.2, P501.6, U501.4
unnamed: D205.2, D206.1, R204.1, R209.2, R247.2
unnamed: D207.1, R206.1, R208.1, U201.4
unnamed: D207.2, D208.1
unnamed: D208.2, R204.2, R210.2, U201.6
unnamed: D209.1, R215.1, U205.4
unnamed: D209.2, D210.1
unnamed: D210.2, U205.6, U207.3
unnamed: D213.2, D214.1, P204.2, U218.2
unnamed: D302.1, Q301.2, R301.2
unnamed: F201.1, P201.1
unnamed: F202.1, P202.1
unnamed: F501.2, P501.1
unnamed: JP201.1, U209.4
unnamed: P203.1, R205.2, R207.2
unnamed: P203.2, R215.2, R217.2, VR201.1, VR202.1, VR203.1, VR204.1
unnamed: P401.1, R401.1
unnamed: P402.1, R402.1
unnamed: P403.1, R403.1
unnamed: P404.1, R404.1
unnamed: P405.1, R405.1
unnamed: P407.1, R401.2
unnamed: P407.2, R402.2
unnamed: P407.3, R403.2
unnamed: P407.4, R404.2
unnamed: P407.5, R405.2
unnamed: Q101.1, R105.1, U101.36
unnamed: Q101.3, U102.8
unnamed: Q301.1, Q302.3, R301.1
unnamed: Q501.3, R503.1
unnamed: Q502.1, R507.1, U502.3
unnamed: R203.2, U201.1
unnamed: R205.1, R206.2, R207.1, R208.2
unnamed: R209.1, U203.3
unnamed: R210.1, U203.2
unnamed: R211.2, U205.1
unnamed: R212.2, U203.1
unnamed: R213.1, U204.2
unnamed: R213.2, R214.2, U203.5
unnamed: R214.1, U206.2
unnamed: R216.1, U208.1
unnamed: R216.2, U207.1, U207.2
unnamed: R217.1, R220.1
unnamed: R218.1, R219.2, R224.2, R232.2, R234.2, U207.10
unnamed: R218.2, R221.2
unnamed: R219.1, U209.2
unnamed: R220.2, R222.2
unnamed: R221.1, R223.1
unnamed: R222.1, R226.1
unnamed: R223.2, R227.2
unnamed: R224.1, R225.1, R225.2, U211.2
unnamed: R226.2, R229.2
unnamed: R227.1, R230.1
unnamed: R228.2, R231.2, R233.2, R238.2, U207.6
unnamed: R229.1, R230.2
unnamed: R231.1, U213.2
unnamed: R232.1, U214.2
unnamed: R233.1, U215.2
unnamed: R234.1, R236.1
unnamed: R235.1, U216.2
unnamed: R235.2, R237.1, R237.2, R240.1, R240.2, R242.1, R242.2, R243.1, R244.1, R244.2
unnamed: R236.2, R239.2
unnamed: R238.1, U217.2
unnamed: R239.1, R241.1
unnamed: R241.2, R243.2
unnamed: R247.1, U202.1, U202.2
unnamed: R248.1, U202.6, U202.7
unnamed: R248.2, U218.1
unnamed: R503.2, R506.2, U502.6
unnamed: R504.2, U502.8
unnamed: R508.1, U502.4
unnamed: SP101.1, U101.22
unnamed: U101.37, U102.3
unnamed: U101.38, U102.7, U102.13
unnamed: U101.39, U102.9, U102.12
unnamed: U101.40, U102.6, U102.11
unnamed: U101.53, U102.10
unnamed: U101.54, U102.5
unnamed: U207.5, U208.2, U210.1, U212.1

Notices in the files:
new_PCBs/ohdsp_OHDSP-ADAU1452/raw.kicad_pcb:
Copyright Paul Janicki 2015
Licensed under the TAPR Open Hardware License (www.tapr.org/OHL).
new_PCBs/open-source-multimeter_Multimeter/raw.kicad_pcb:
Licensed under the GNU GPL v3
